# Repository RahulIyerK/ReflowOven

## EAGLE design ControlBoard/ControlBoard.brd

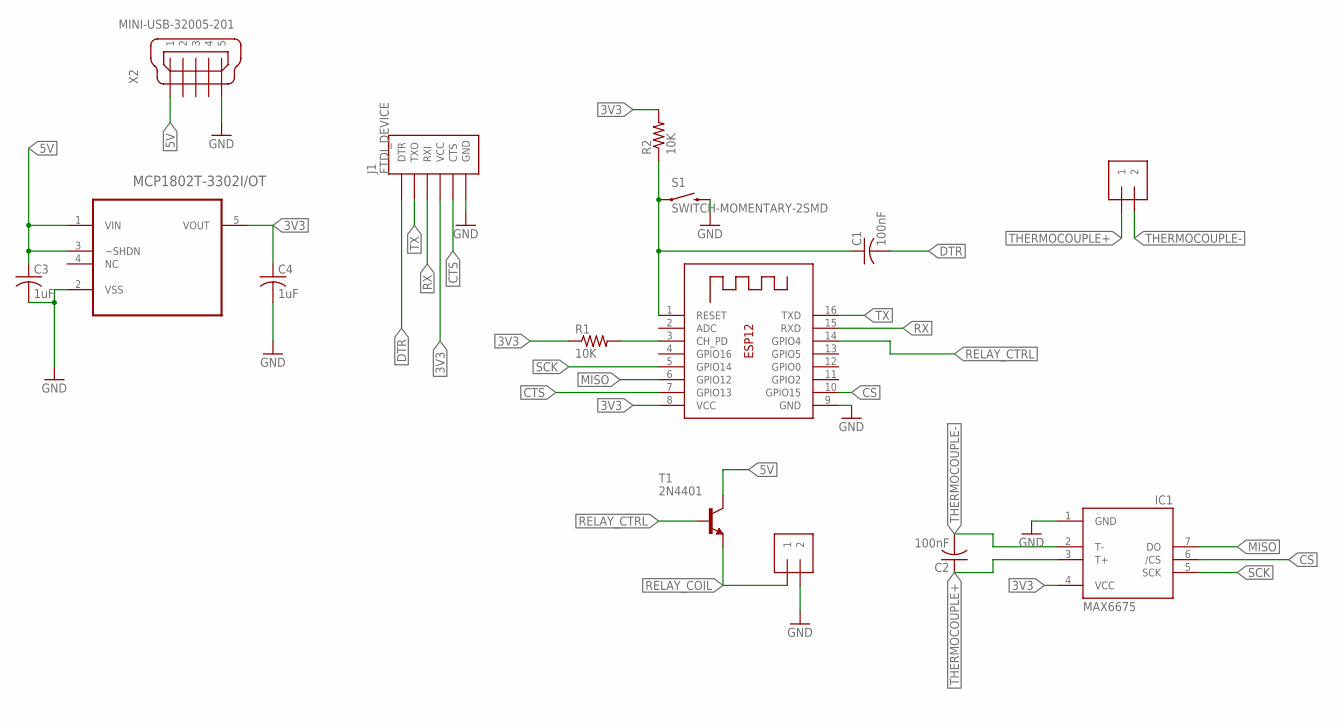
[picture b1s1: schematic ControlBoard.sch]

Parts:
C1, C2: 100nF; C0603
C3, C4: 1uF; C0603
IC1: MAX6675; SO08
J1: FTDI_DEVICE; FTDI_DEVICE_SIDE
J2, J3: 1X2-3.5MM
MCP1802T-3302I/OT: MCP1802T-3002I/OT; SOT95P270X145-5N
R1, R2: 10K; R0603
S1: SWITCH-MOMENTARY-2SMD; TACTILE-SWITCH-SMD
T1: 2N4401; TO92-EBC
X1: ESP-12
X2: MINI-USB-32005-201; 32005-201

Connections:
3V3: C4.1, IC1.4 (VCC), J1.P$4 (VCC), MCP1802T-3302I/OT.5 (VOUT), R1.1, R2.2, X1.8 (VCC)
5V: C3.1, MCP1802T-3302I/OT.1 (VIN), MCP1802T-3302I/OT.3 (~SHDN), T1.C, X2.1
CH_PD: R1.2, X1.3 (CH_PD)
CS: IC1.6 (/CS), X1.10 (GPIO15)
CTS: J1.P$5 (CTS), X1.7 (GPIO13)
DTR: C1.2, J1.P$1 (DTR)
GND: C3.2, C4.2, IC1.1 (GND), J1.P$6 (GND), J3.2, MCP1802T-3302I/OT.2 (VSS), S1.3 (2), X1.9 (GND), X2.5
MISO: IC1.7 (DO), X1.6 (GPIO12)
RELAY_COIL: J3.1, T1.E
RELAY_CTRL: T1.B, X1.14 (GPIO4)
RST: C1.1, R2.1, S1.1, X1.1 (RESET)
RX: J1.P$3 (RXI), X1.15 (RXD)
SCK: IC1.5 (SCK), X1.5 (GPIO14)
THERMOCOUPLE+: C2.1, IC1.3 (T+), J2.1
THERMOCOUPLE-: C2.2, IC1.2 (T-), J2.2
TX: J1.P$2 (TXO), X1.16 (TXD)

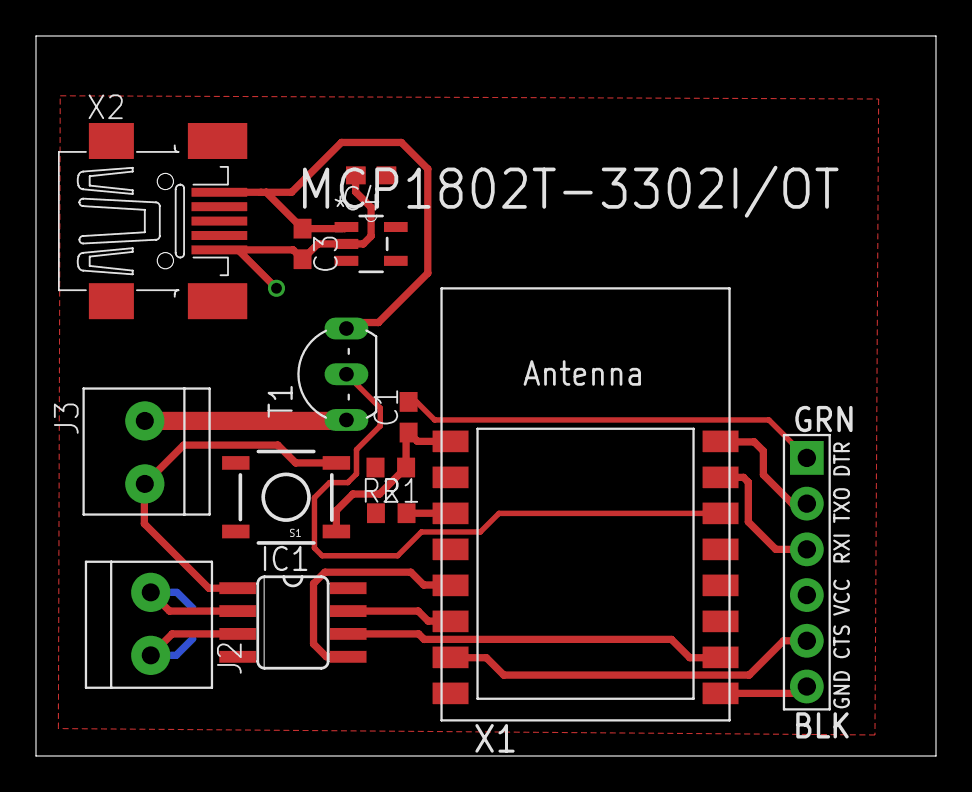
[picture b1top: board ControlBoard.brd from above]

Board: 2 copper layers, 50.0 x 40.0 mm, 15 parts (1 on the bottom side), 16 nets.

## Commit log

2017-02-22 yo dog
2017-02-22 format
2017-02-22 test commit for demo purposes
2017-03-07 added schematic file
2017-03-07 added board file
2017-03-07 added git_help.txt (contains basic git use instructions)
2017-03-07 removed eagle backup files
2017-03-07 updates to control board...needs more work
2017-03-09 added thermocouple-digital chip
2017-04-04 updated eagle board and schematic files
2017-04-05 test Arduino file for ESP8266 Ticker Library
2017-04-07 Ticker library test...have watchdog issues :(
2017-04-11 updates to ticker test
2017-04-12 more modifications to Ticker
2017-04-12 more updates to ticker
2017-04-12 pushing library memes
2017-04-12 more updates
2017-05-07 added reflow sample file (Derek)
2017-05-15 PID_Pseudo
2017-05-15 pid file from worksession
2017-05-15 teaching cullen git is cancer
2017-05-15 cleaned up code...need to clean up more
2017-05-17 added web server
2017-05-17 added web server file
2017-05-17 cleaned up code, added comments, and changed temperature integer size to match the library output integer size
2017-05-17 uin16_t to hold values of temperature, not uint32_t... (fixed bug from previous commit)
2017-05-18 update web server
2017-05-18 cleanup and changed server initialization function's name
2017-05-19 put some pid functions in main
2017-05-25 cleaned some stuff up
